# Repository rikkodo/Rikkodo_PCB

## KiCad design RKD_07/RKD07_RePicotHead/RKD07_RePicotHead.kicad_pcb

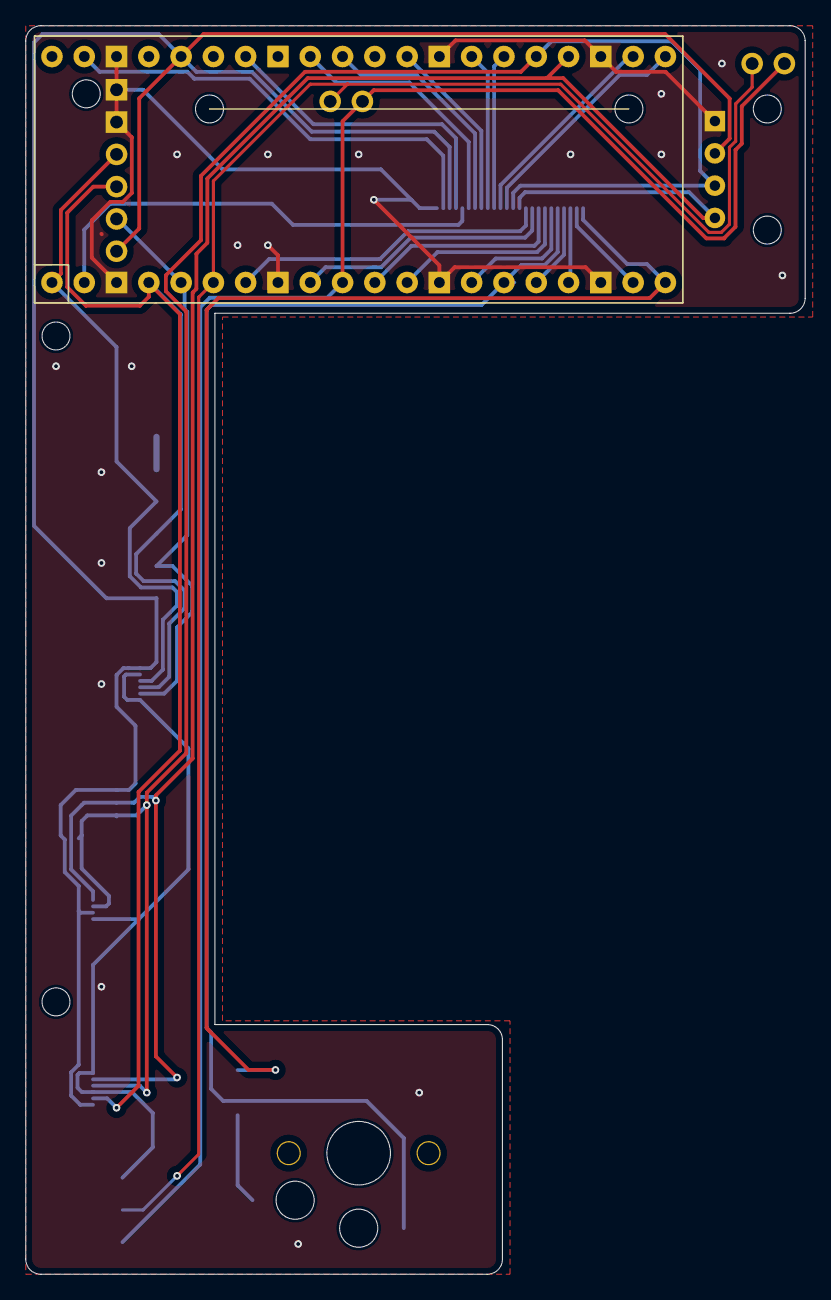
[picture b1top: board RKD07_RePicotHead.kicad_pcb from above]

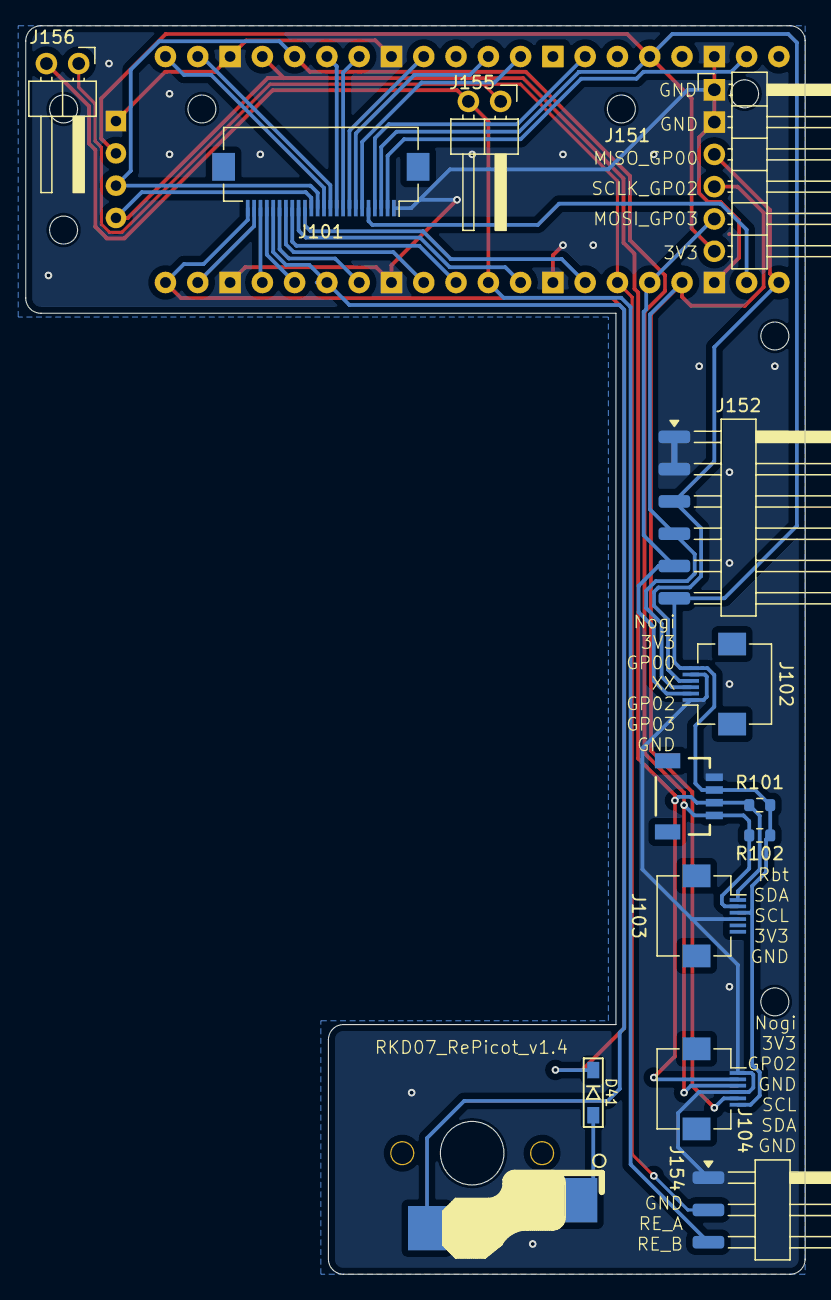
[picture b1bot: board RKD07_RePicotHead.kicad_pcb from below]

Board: 2 copper layers, 61.3 x 98.2 mm, 22 parts (12 on the bottom side), 30 nets.

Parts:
D41: D; Diode_SMD
J101: Conn_01x24; Hirose_FH12-24S-0.5SH_1x24-1MP_P0.50mm_Horizontal
J102, J103, J104: Conn_01x06; Hirose_FH12-6S-0.5SH_1x06-1MP_P0.50mm_Horizontal
J151: Conn_01x06; PinHeader_1x06_P2.54mm_Horizontal
J152: Conn_01x06; Harwin_M20-89006xx_1x06_P2.54mm_Horizontal
J153: Qwiic_RA; JST_SMD_1.0mm-4_Black
J154: Conn_01x02_Socket; Harwin_M20-89003xx_1x03_P2.54mm_Horizontal
J155, J156: Conn_01x02_Socket; PinHeader_1x02_P2.54mm_Horizontal
OL101: OLED; OLED_center_display
R101, R102: 1kΩ; R_0603_1608Metric
Ref**: Val**; m2_Screw_Hole
Ref**#2, Ref**#3, Ref**#4, Ref**#5: Val**; m2_Screw_Hole
SW41: SW_Push; rkd_Asm_ChocV1V2_Hotswap_1u
U101: Pico; rkd_RPi_Pico_TH_NODBG
UnifiedW**: rkd_unified_wid_BTM

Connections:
3V3: J101.3, J102.6, J103.3, J104.6, J151.6, J152.6, J153.2, OL101.3 (VCC), R101.1, R102.1, U101.36 (3V3)
COL0_L: J101.15, U101.7 (GPIO5)
COL1_L: J101.16, U101.9 (GPIO6)
COL2_L: J101.17, U101.11 (GPIO8)
COL3_L: J101.18, U101.12 (GPIO9)
COL4_L: J101.19, U101.14 (GPIO10)
COL5_L: J101.20, SW41.2, U101.15 (GPIO11)
COL6_L: J101.12, U101.21 (GPIO16)
COL7_L: J101.11, U101.22 (GPIO17)
COL8_L: J101.10, U101.26 (GPIO20)
COL9_L: J101.9, U101.27 (GPIO21)
COL10_L: J101.8, U101.29 (GPIO22)
COL11_L: J101.7, U101.31 (GPIO26_ADC0)
COL12_L: J101.6, U101.32 (GPIO27_ADC1)
COL13_L: J101.5, U101.2 (GPIO1)
GND: J101.1, J102.1, J102.5, J103.4, J104.1, J104.4, J151.1, J151.2, J152.1, J152.2, J153.1, J154.1, OL101.4 (GND), U101.3 (GND), U101.8 (GND), U101.13 (GND), U101.18 (GND), U101.23 (GND), U101.28 (GND), U101.38 (GND)
GP00_MISO: J102.4, J151.3, J152.3, U101.1 (GPIO0)
GP02_SCLK: J102.3, J104.5, J151.4, J152.4, U101.4 (GPIO2)
GP03_MOSI: J102.2, J151.5, J152.5, U101.5 (GPIO3)
GP04: J154.2, J155.1, J156.1, U101.6 (GPIO4)
GP07: J154.3, J155.2, J156.2, U101.10 (GPIO7)
unnamed: D41.2 (A), SW41.1
ROW0_L: J101.4, U101.34 (GPIO28_ADC2)
ROW1_L: J101.21, U101.16 (GPIO12)
ROW2_L: J101.22, U101.17 (GPIO13)
ROW3_L: J101.23, U101.19 (GPIO14)
ROW4_L: D41.1 (K), J101.24, U101.20 (GPIO15)
SCL/TX_L: J101.13, J103.2, J104.3, J153.4, OL101.2 (SCL), R102.2, U101.25 (GPIO19)
SDA/SCK_L: J101.14, J103.1, J104.2, J153.3, OL101.1 (SDA), R101.2, U101.24 (GPIO18)
VCC: J101.2, U101.39 (VSYS)

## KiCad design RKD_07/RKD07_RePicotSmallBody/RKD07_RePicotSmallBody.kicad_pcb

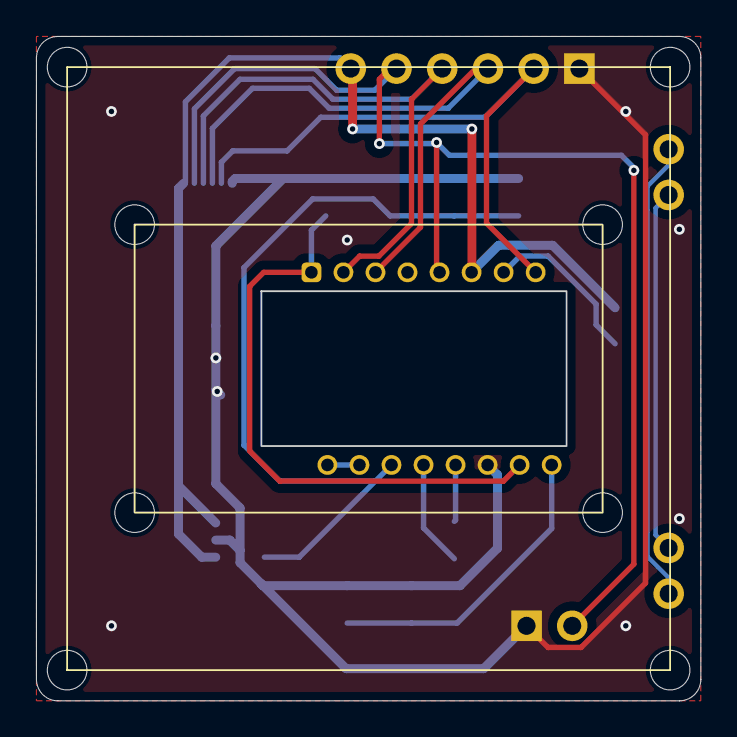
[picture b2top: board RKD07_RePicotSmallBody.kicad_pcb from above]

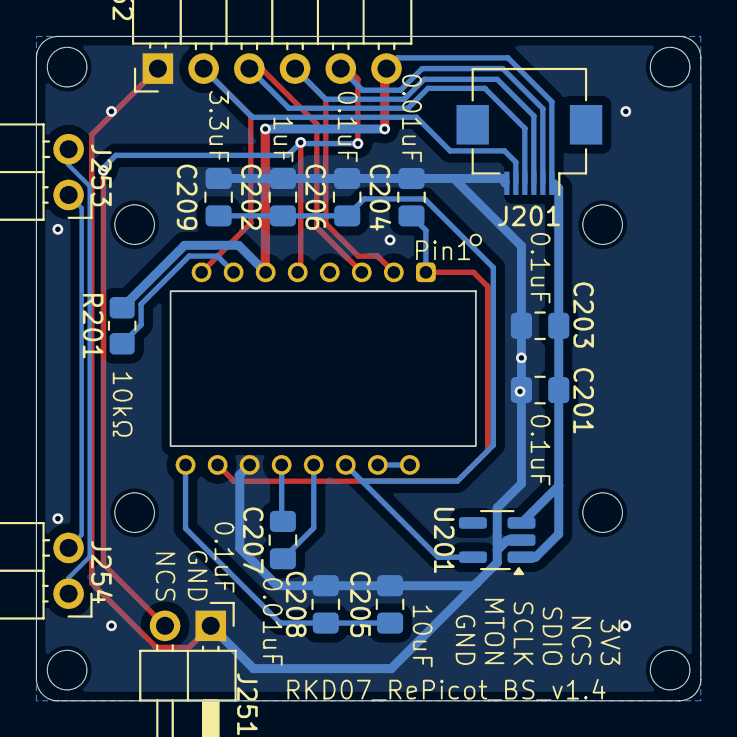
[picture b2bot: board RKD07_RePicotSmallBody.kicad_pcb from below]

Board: 2 copper layers, 36.9 x 36.9 mm, 18 parts (16 on the bottom side), 15 nets.

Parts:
C201, C203, C206, C207: 0.1uF X7R; C_0805_2012Metric_Pad1.18x1.45mm_HandSolder
C202: 1uF; C_0805_2012Metric_Pad1.18x1.45mm_HandSolder
C204, C208: 0.01uF X7R; C_0805_2012Metric_Pad1.18x1.45mm_HandSolder
C205: 10uF X7R; C_0805_2012Metric_Pad1.18x1.45mm_HandSolder
C209: 3.3uF/16V; C_0805_2012Metric_Pad1.18x1.45mm_HandSolder
J201: Conn_01x06; Hirose_FH12-6S-0.5SH_1x06-1MP_P0.50mm_Horizontal
J251, J253, J254: Conn_01x02_Socket; PinHeader_1x02_P2.54mm_Horizontal
J252: Conn_01x06; PinHeader_1x06_P2.54mm_Horizontal
Picot**: rkd_picot5400_BTM
R201: 10k; R_0805_2012Metric_Pad1.20x1.40mm_HandSolder
U201: TLV70019DDCR; SOT-23-5_HandSoldering
U202: PMW3610DM-SUDU

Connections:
1V9_E: C202.1, C206.1, C209.1, U201.5 (OUT), U202.14 (VDD)
3V3_E: C201.1, C203.1, J201.1, J252.6, R201.2, U201.1 (IN), U201.3 (EN), U202.6 (VDDIO)
GND_E: C201.2, C202.2, C203.2, C204.2, C205.2, C206.2, C208.2, C209.2, J201.6, J251.1, J252.1, U201.2 (GND), U202.11 (GND)
GP00_MISO_E: J201.3, J252.4, U202.2 (SDIO)
GP02_SCLK_E: J201.4, J252.3, U202.3 (SCLK)
GP03_MOSI_E: J201.5, J252.2, U202.8 (MOTION)
GP04_E: J253.1, J254.2
GP07_E: J253.2, J254.1
NCS_E: J201.2, J251.2, J252.5, U202.5 (NCS)
unnamed: C204.1, U202.1 (+VCSEL), U202.10 (PASS_T)
unnamed: U202.15 (XYLASER), U202.16 (-VCSEL)
unnamed: C207.1, U202.13 (CN)
unnamed: C207.2, U202.12 (CP)
unnamed: R201.1, U202.7 (NRESET)
unnamed: C205.1, C208.1, U202.9 (VCP)

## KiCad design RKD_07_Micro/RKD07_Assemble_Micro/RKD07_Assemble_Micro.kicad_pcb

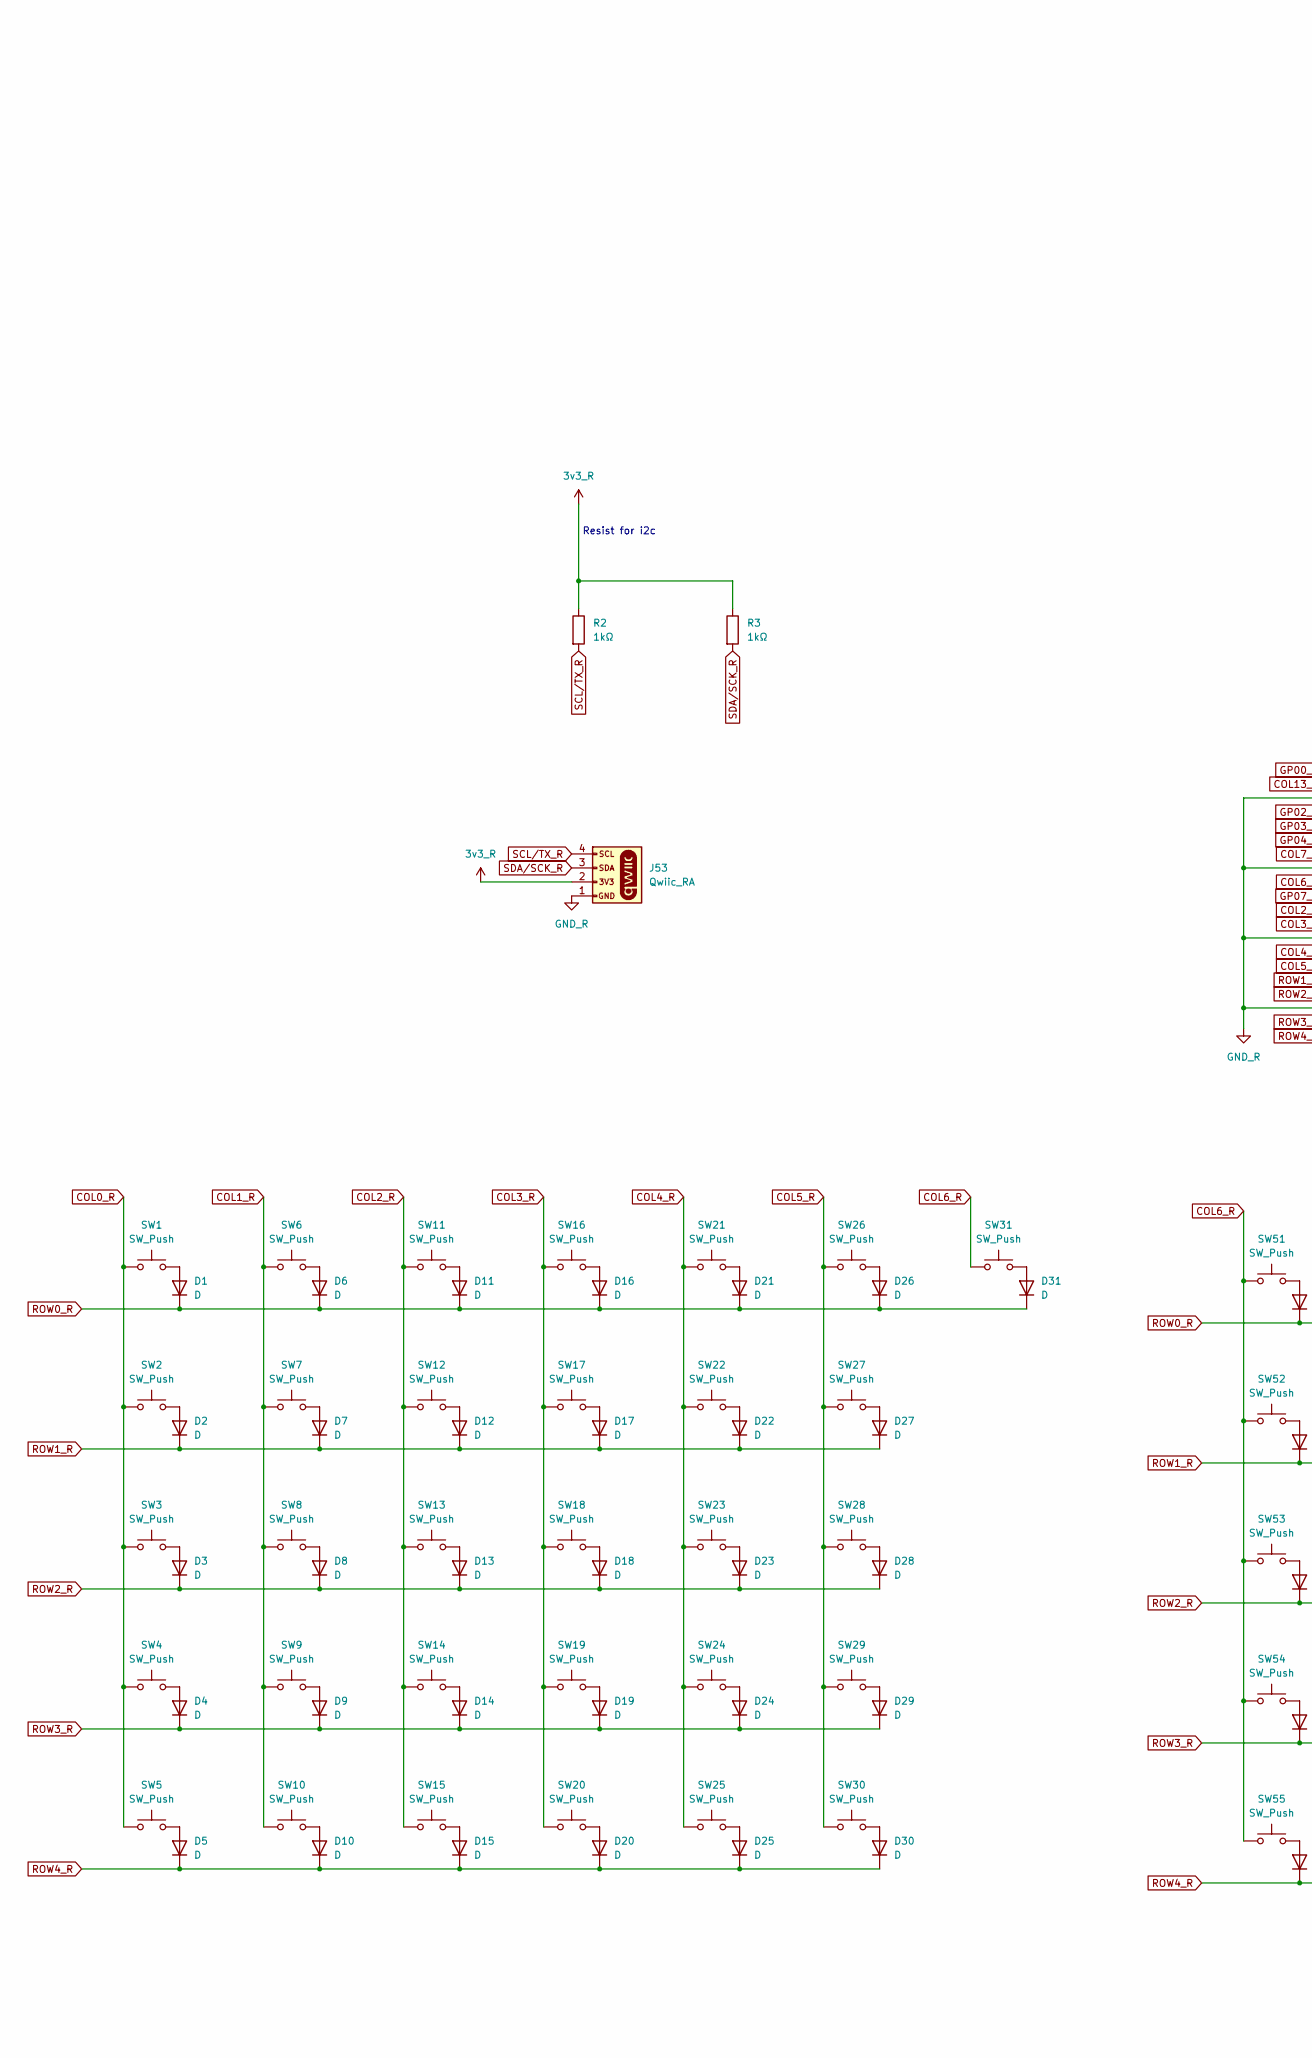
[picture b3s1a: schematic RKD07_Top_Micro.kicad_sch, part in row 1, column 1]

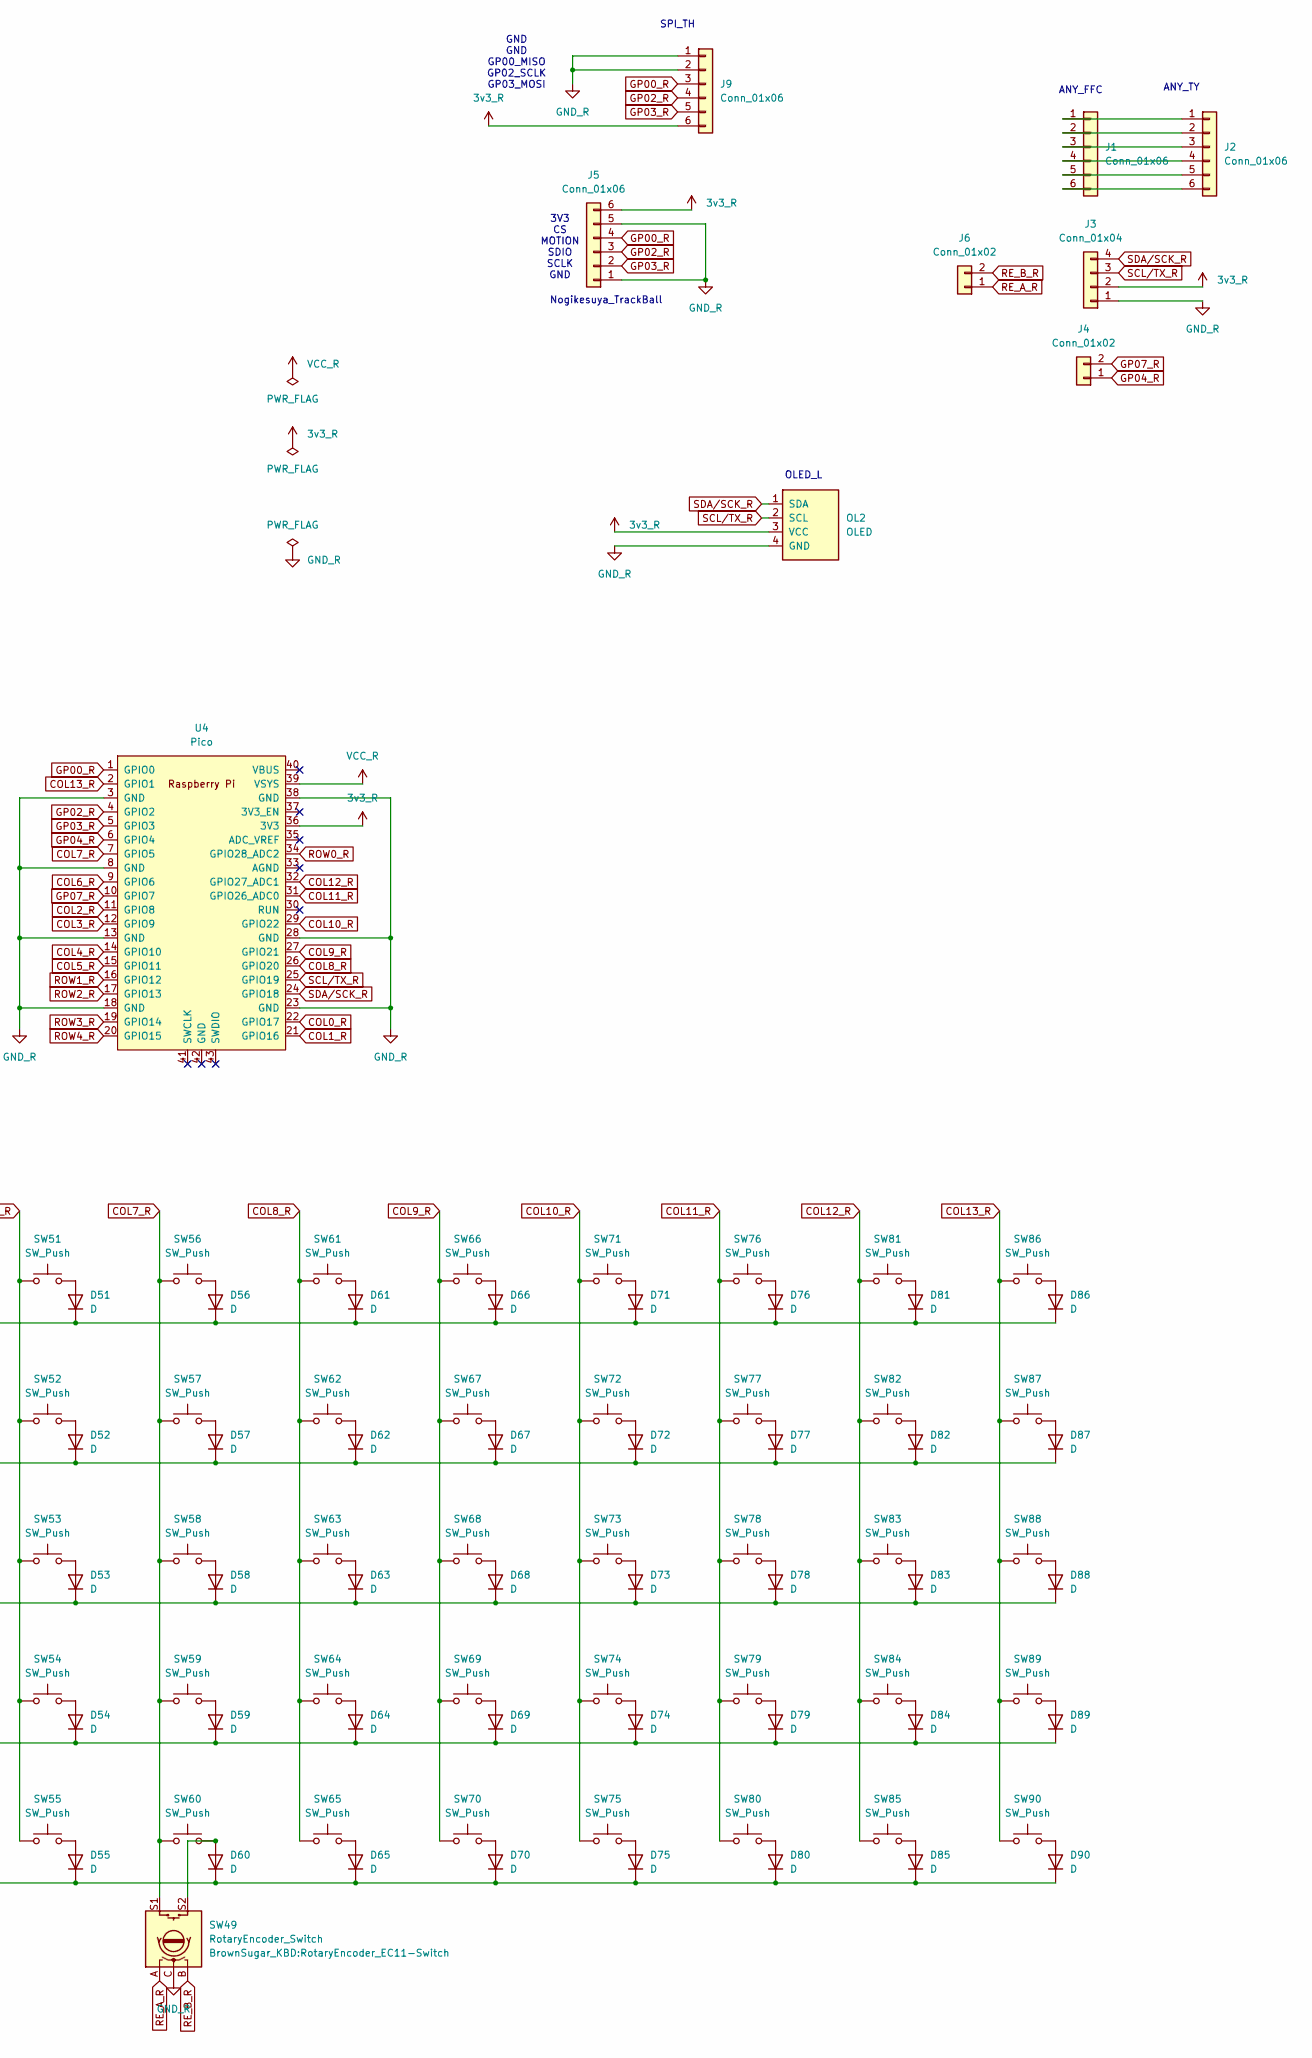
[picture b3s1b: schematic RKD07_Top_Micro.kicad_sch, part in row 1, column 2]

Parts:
D1, D2, D3, D4, D5, D6, D7, D8, D9, D10, D11, D12, D13, D14, D15, D16, D17, D18, D19, D20, D21, D22, D23, D24, D25, D26, D27, D28, D29, D30, D31, D51, D52, D53, D54, D55, D56, D57, D58, D59, D60, D61, D62, D63, D64, D65, D66, D67, D68, D69, D70, D71, D72, D73, D74, D75, D76, D77, D78, D79, D80, D81, D82, D83, D84, D85, D86, D87, D88, D89, D90: D; Diode_SMD
J1, J5: Conn_01x06; Hirose_FH12-6S-0.5SH_1x06-1MP_P0.50mm_Horizontal
J2, J9: Conn_01x06; PinHeader_1x06_P2.54mm_Vertical
J3: Conn_01x04; PinHeader_1x04_P2.54mm_Vertical
J4, J6: Conn_01x02; PinHeader_1x02_P2.54mm_Vertical
J53: Qwiic_RA; JST_SMD_1.0mm-4_Black
OL2: OLED; OLED_center_display
R2, R3: 1kΩ; R_0603_1608Metric
SW1, SW6, SW7, SW8, SW9, SW11, SW12, SW13, SW14, SW16, SW17, SW18, SW19, SW21, SW22, SW23, SW24, SW26, SW27, SW28, SW29, SW31, SW51, SW52, SW54, SW56, SW57, SW58, SW59, SW61, SW62, SW63, SW64, SW66, SW67, SW68, SW69, SW70, SW71, SW72, SW73, SW74, SW75, SW76, SW77, SW78, SW79, SW80, SW81, SW82, SW83, SW84, SW85, SW89, SW90: SW_Push; rkd_pushsw_2_1u
SW2, SW60, SW87: SW_Push; rkd_pushsw_2_1.5u
SW3: SW_Push; rkd_pushsw_2_1.75u
SW4, SW86: SW_Push; rkd_pushsw_2_2u
SW5, SW10, SW15, SW20, SW30, SW53, SW55, SW65: SW_Push; rkd_pushsw_2_1.25u
SW25, SW88: SW_Push; rkd_pushsw_2_2.25u
SW49: RotaryEncoder_Switch; RotaryEncoder_EC11-Switch
U4: Pico; rkd_RPi_Pico_TH_NODBG

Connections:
3v3_R: J3.2, J5.6, J9.6, J53.2, OL2.3 (VCC), R2.1, R3.1, U4.36 (3V3)
COL0_R: SW1.2, SW2.2, SW3.2, SW4.2, SW5.2, U4.22 (GPIO17)
COL1_R: SW6.2, SW7.2, SW8.2, SW9.2, SW10.2, U4.21 (GPIO16)
COL2_R: SW11.2, SW12.2, SW13.2, SW14.2, SW15.2, U4.11 (GPIO8)
COL3_R: SW16.2, SW17.2, SW18.2, SW19.2, SW20.2, U4.12 (GPIO9)
COL4_R: SW21.2, SW22.2, SW23.2, SW24.2, SW25.2, U4.14 (GPIO10)
COL5_R: SW26.2, SW27.2, SW28.2, SW29.2, SW30.2, U4.15 (GPIO11)
COL6_R: SW31.2, SW51.2, SW52.2, SW53.2, SW54.2, SW55.2, U4.9 (GPIO6)
COL7_R: SW49.S1, SW56.2, SW57.2, SW58.2, SW59.2, SW60.2, U4.7 (GPIO5)
COL8_R: SW61.2, SW62.2, SW63.2, SW64.2, SW65.2, U4.26 (GPIO20)
COL9_R: SW66.2, SW67.2, SW68.2, SW69.2, SW70.2, U4.27 (GPIO21)
COL10_R: SW71.2, SW72.2, SW73.2, SW74.2, SW75.2, U4.29 (GPIO22)
COL11_R: SW76.2, SW77.2, SW78.2, SW79.2, SW80.2, U4.31 (GPIO26_ADC0)
COL12_R: SW81.2, SW82.2, SW83.2, SW84.2, SW85.2, U4.32 (GPIO27_ADC1)
COL13_R: SW86.2, SW87.2, SW88.2, SW89.2, SW90.2, U4.2 (GPIO1)
GND_R: J3.1, J5.1, J5.5, J9.1, J9.2, J53.1, OL2.4 (GND), SW49.C, U4.3 (GND), U4.8 (GND), U4.13 (GND), U4.18 (GND), U4.23 (GND), U4.28 (GND), U4.38 (GND)
GP00_R: J5.4, J9.3, U4.1 (GPIO0)
GP02_R: J5.3, J9.4, U4.4 (GPIO2)
GP03_R: J5.2, J9.5, U4.5 (GPIO3)
GP04_R: J4.1, U4.6 (GPIO4)
GP07_R: J4.2, U4.10 (GPIO7)
unnamed: D1.2 (A), SW1.1
unnamed: D2.2 (A), SW2.1
unnamed: D3.2 (A), SW3.1
unnamed: D4.2 (A), SW4.1
unnamed: D5.2 (A), SW5.1
unnamed: D6.2 (A), SW6.1
unnamed: D7.2 (A), SW7.1
unnamed: D8.2 (A), SW8.1
unnamed: D9.2 (A), SW9.1
unnamed: D10.2 (A), SW10.1
unnamed: D11.2 (A), SW11.1
unnamed: D12.2 (A), SW12.1
unnamed: D13.2 (A), SW13.1
unnamed: D14.2 (A), SW14.1
unnamed: D15.2 (A), SW15.1
unnamed: D16.2 (A), SW16.1
unnamed: D17.2 (A), SW17.1
unnamed: D18.2 (A), SW18.1
unnamed: D19.2 (A), SW19.1
unnamed: D20.2 (A), SW20.1
unnamed: D21.2 (A), SW21.1
unnamed: D22.2 (A), SW22.1
unnamed: D23.2 (A), SW23.1
unnamed: D24.2 (A), SW24.1
unnamed: D25.2 (A), SW25.1
unnamed: D26.2 (A), SW26.1
unnamed: D27.2 (A), SW27.1
unnamed: D28.2 (A), SW28.1
unnamed: D29.2 (A), SW29.1
unnamed: D30.2 (A), SW30.1
unnamed: D31.2 (A), SW31.1
unnamed: D51.2 (A), SW51.1
unnamed: D52.2 (A), SW52.1
unnamed: D53.2 (A), SW53.1
unnamed: D54.2 (A), SW54.1
unnamed: D55.2 (A), SW55.1
unnamed: D56.2 (A), SW56.1
unnamed: D57.2 (A), SW57.1
unnamed: D58.2 (A), SW58.1
unnamed: D59.2 (A), SW59.1
unnamed: D60.2 (A), SW49.S2, SW60.1
unnamed: D61.2 (A), SW61.1
unnamed: D62.2 (A), SW62.1
unnamed: D63.2 (A), SW63.1
unnamed: D64.2 (A), SW64.1
unnamed: D65.2 (A), SW65.1
unnamed: D66.2 (A), SW66.1
unnamed: D67.2 (A), SW67.1
unnamed: D68.2 (A), SW68.1
unnamed: D69.2 (A), SW69.1
unnamed: D70.2 (A), SW70.1
unnamed: D71.2 (A), SW71.1
unnamed: D72.2 (A), SW72.1
unnamed: D73.2 (A), SW73.1
unnamed: D74.2 (A), SW74.1
unnamed: D75.2 (A), SW75.1
unnamed: D76.2 (A), SW76.1
unnamed: D77.2 (A), SW77.1
unnamed: D78.2 (A), SW78.1
unnamed: D79.2 (A), SW79.1
unnamed: D80.2 (A), SW80.1
unnamed: D81.2 (A), SW81.1
unnamed: D82.2 (A), SW82.1
unnamed: D83.2 (A), SW83.1
unnamed: D84.2 (A), SW84.1
unnamed: D85.2 (A), SW85.1
unnamed: D86.2 (A), SW86.1
unnamed: D87.2 (A), SW87.1
unnamed: D88.2 (A), SW88.1
unnamed: D89.2 (A), SW89.1
unnamed: D90.2 (A), SW90.1
unnamed: J1.1, J2.1
unnamed: J1.2, J2.2
unnamed: J1.3, J2.3
unnamed: J1.4, J2.4
unnamed: J1.5, J2.5
unnamed: J1.6, J2.6
RE_A_R: J6.1, SW49.A
RE_B_R: J6.2, SW49.B
ROW0_R: D1.1 (K), D6.1 (K), D11.1 (K), D16.1 (K), D21.1 (K), D26.1 (K), D31.1 (K), D51.1 (K), D56.1 (K), D61.1 (K), D66.1 (K), D71.1 (K), D76.1 (K), D81.1 (K), D86.1 (K), U4.34 (GPIO28_ADC2)
ROW1_R: D2.1 (K), D7.1 (K), D12.1 (K), D17.1 (K), D22.1 (K), D27.1 (K), D52.1 (K), D57.1 (K), D62.1 (K), D67.1 (K), D72.1 (K), D77.1 (K), D82.1 (K), D87.1 (K), U4.16 (GPIO12)
ROW2_R: D3.1 (K), D8.1 (K), D13.1 (K), D18.1 (K), D23.1 (K), D28.1 (K), D53.1 (K), D58.1 (K), D63.1 (K), D68.1 (K), D73.1 (K), D78.1 (K), D83.1 (K), D88.1 (K), U4.17 (GPIO13)
ROW3_R: D4.1 (K), D9.1 (K), D14.1 (K), D19.1 (K), D24.1 (K), D29.1 (K), D54.1 (K), D59.1 (K), D64.1 (K), D69.1 (K), D74.1 (K), D79.1 (K), D84.1 (K), D89.1 (K), U4.19 (GPIO14)
ROW4_R: D5.1 (K), D10.1 (K), D15.1 (K), D20.1 (K), D25.1 (K), D30.1 (K), D55.1 (K), D60.1 (K), D65.1 (K), D70.1 (K), D75.1 (K), D80.1 (K), D85.1 (K), D90.1 (K), U4.20 (GPIO15)
SCL/TX_R: J3.3, J53.4, OL2.2 (SCL), R2.2, U4.25 (GPIO19)
SDA/SCK_R: J3.4, J53.3, OL2.1 (SDA), R3.2, U4.24 (GPIO18)
VCC_R: U4.39 (VSYS)

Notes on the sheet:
GND GND GP00_MISO GP02_SCLK GP03_MOSI
Resist for i2c
ANY_TY
3V3 CS MOTION SDIO SCLK GND
ANY_FFC
Nogikesuya_TrackBall
SPI_TH
OLED_L

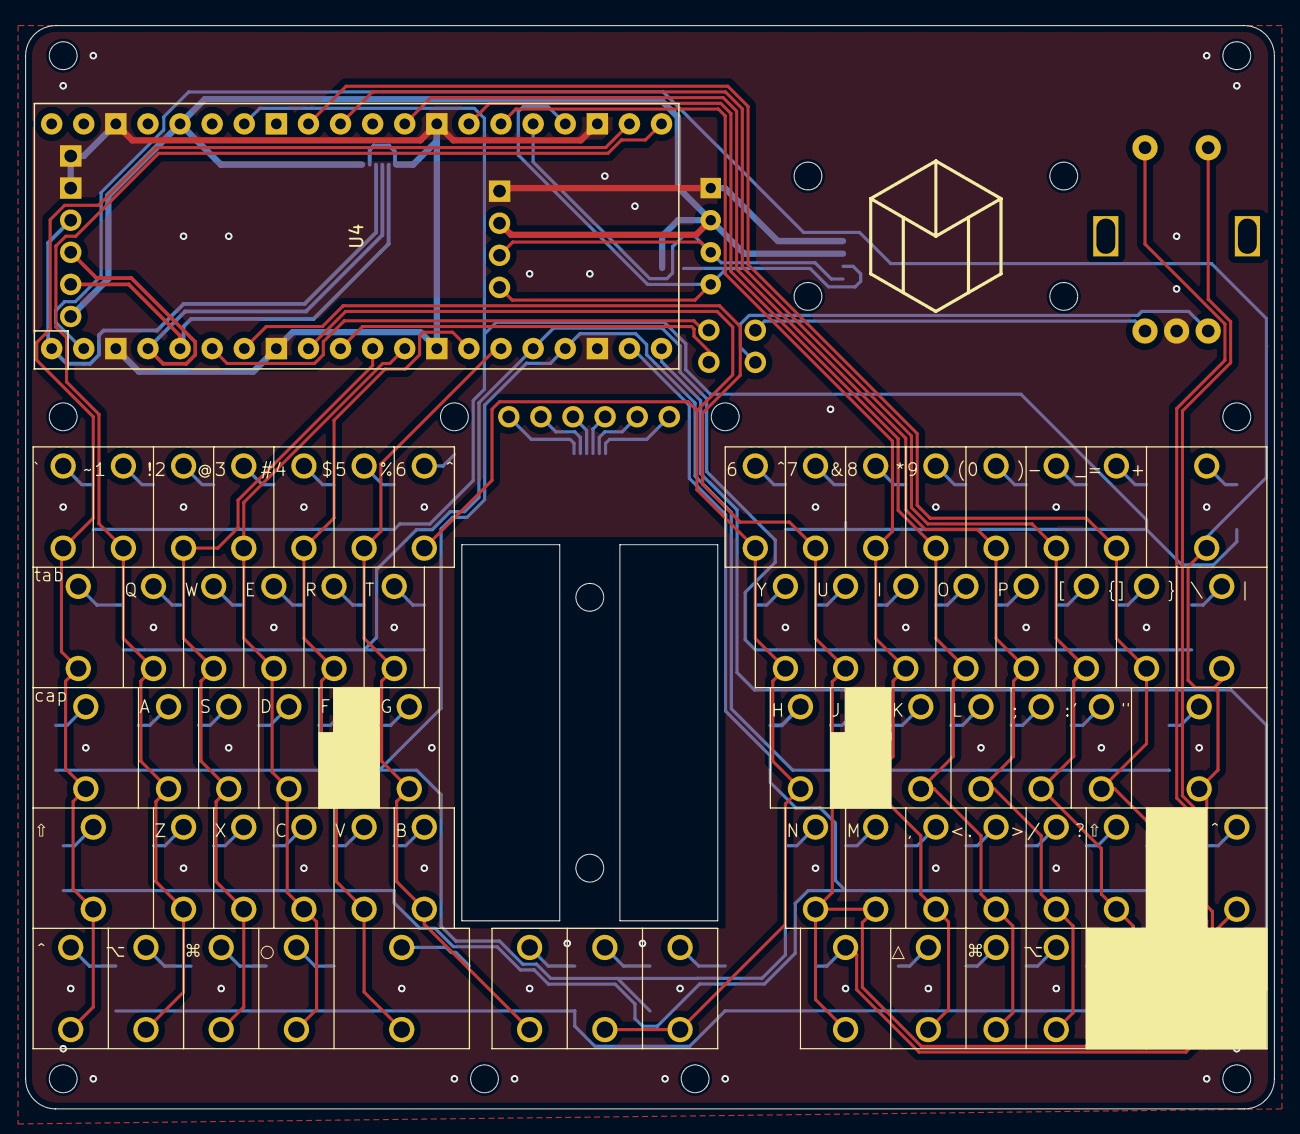
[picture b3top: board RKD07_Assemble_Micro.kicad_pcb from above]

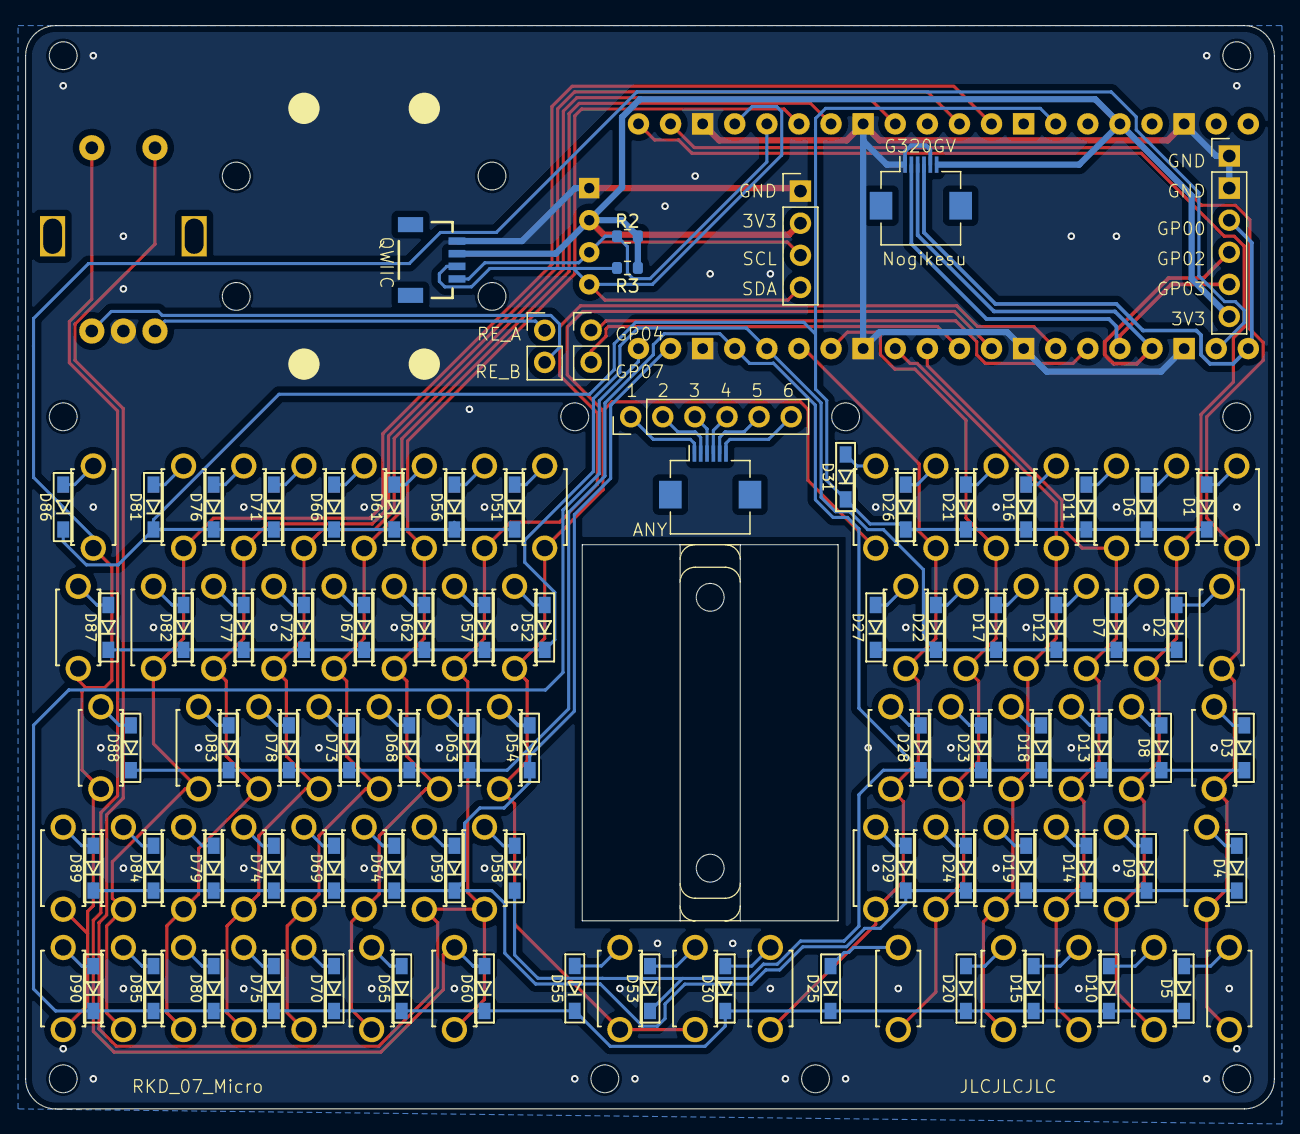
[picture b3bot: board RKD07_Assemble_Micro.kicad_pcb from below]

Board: 2 copper layers, 98.8 x 85.7 mm, 170 parts (10 on the bottom side), 107 nets.

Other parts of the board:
Point1: Guard_Screw_Hall; rkd_Guard_Screw_Hall
Ref**: Val**; m2_Screw_Hole
Ref**#2, Ref**#3, Ref**#4, Ref**#5, Ref**#6, Ref**#7, Ref**#8, Ref**#9, Ref**#10, Ref**#11, Ref**#12, Ref**#13, Ref**#14: Val**; m2_Screw_Hole

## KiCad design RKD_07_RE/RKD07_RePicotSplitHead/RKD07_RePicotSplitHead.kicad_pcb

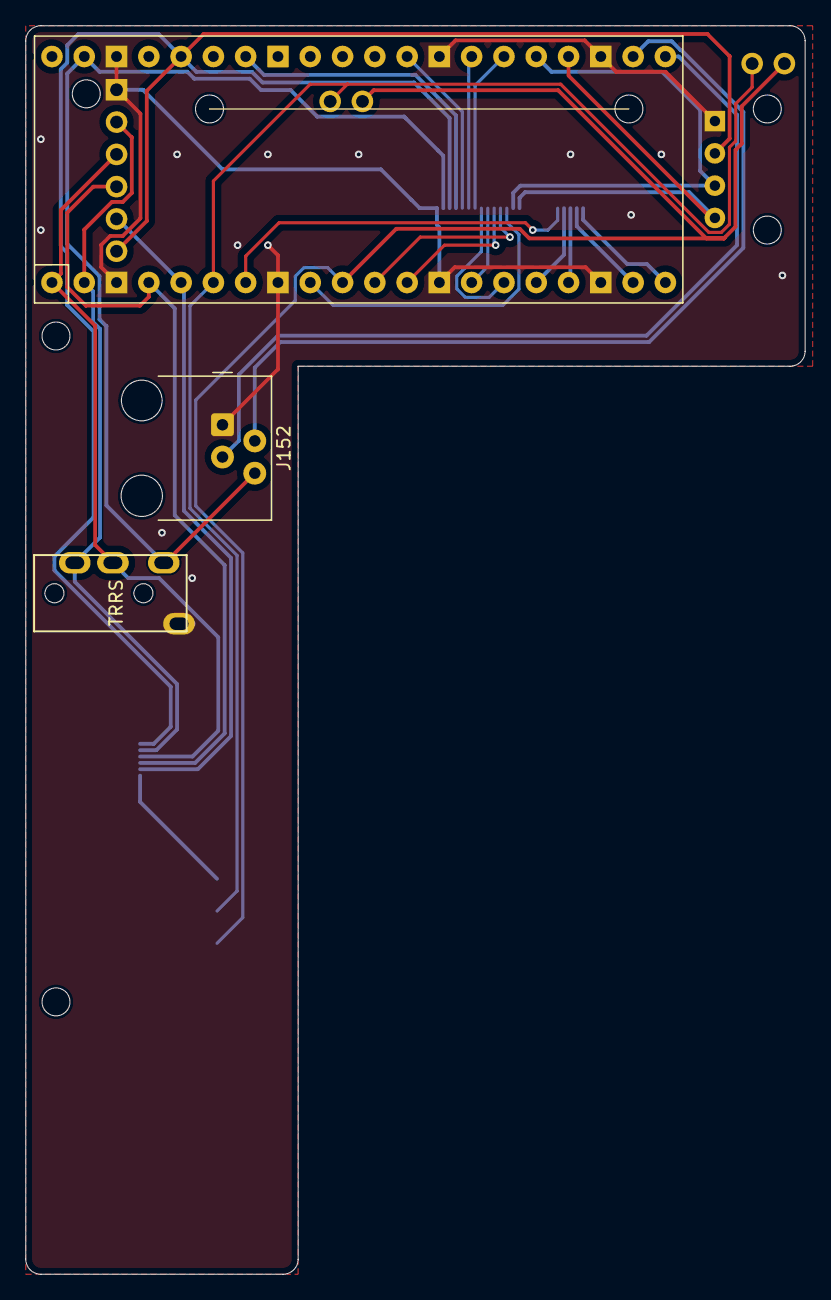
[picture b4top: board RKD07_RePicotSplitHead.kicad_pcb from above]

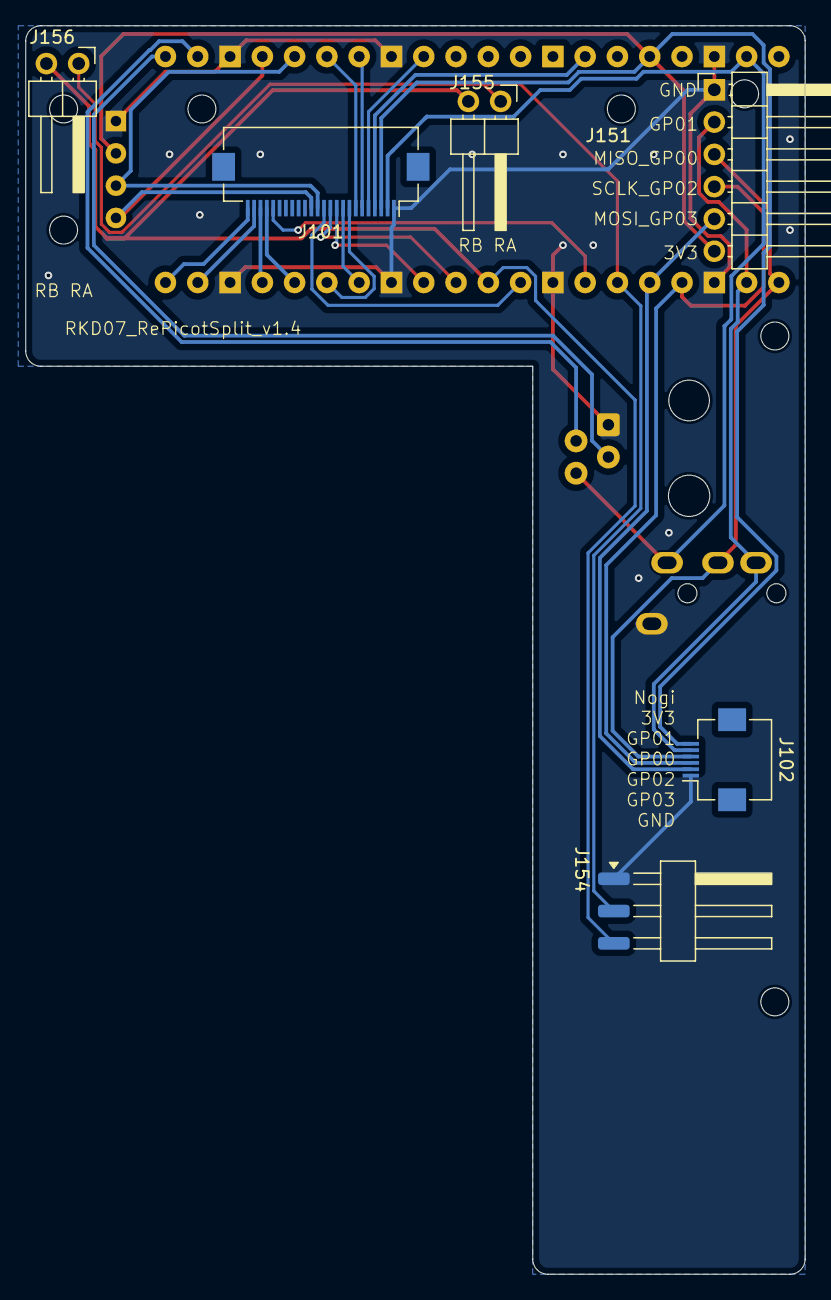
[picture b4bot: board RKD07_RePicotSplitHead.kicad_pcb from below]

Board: 2 copper layers, 61.3 x 98.2 mm, 16 parts (6 on the bottom side), 27 nets.

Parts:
J101: Conn_01x24; Hirose_FH12-24S-0.5SH_1x24-1MP_P0.50mm_Horizontal
J102: Conn_01x06; Hirose_FH12-6S-0.5SH_1x06-1MP_P0.50mm_Horizontal
J151: Conn_01x06; PinHeader_1x06_P2.54mm_Horizontal
J152: RJ9; RJ9_Evercom_5301-440xxx_Horizontal
J153: TRRS; TRRS_PJ-320A
J154: Conn_01x02_Socket; Harwin_M20-89003xx_1x03_P2.54mm_Horizontal
J155, J156: Conn_01x02_Socket; PinHeader_1x02_P2.54mm_Horizontal
OL101: OLED; OLED_center_display
Ref**: Val**; m2_Screw_Hole
Ref**#2, Ref**#3, Ref**#4, Ref**#5: Val**; m2_Screw_Hole
U101: Pico; rkd_RPi_Pico_TH_NODBG
UnifiedW**: rkd_unified_wid_BTM

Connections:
3V3: J101.3, J102.6, J151.6, OL101.3 (VCC), U101.36 (3V3)
COL5_L: J101.20, U101.7 (GPIO5)
COL6_L: J101.12, U101.9 (GPIO6)
COL7_L: J101.11, U101.11 (GPIO8)
COL8_L: J101.10, U101.12 (GPIO9)
COL9_L: J101.9, U101.14 (GPIO10)
COL10_L: J101.8, U101.15 (GPIO11)
COL11_L: J101.7, U101.26 (GPIO20)
COL12_L: J101.6, U101.27 (GPIO21)
COL13_L: J101.5, U101.29 (GPIO22)
GND: J101.1, J102.1, J151.1, J152.1, J153.A, J154.1, OL101.4 (GND), U101.3 (GND), U101.8 (GND), U101.13 (GND), U101.18 (GND), U101.23 (GND), U101.28 (GND), U101.38 (GND)
GP00_MISO: J102.4, J151.3, J153.C, U101.1 (GPIO0)
GP01_NCS: J102.5, J151.2, J153.B, U101.2 (GPIO1)
GP02_SCLK: J102.3, J151.4, U101.4 (GPIO2)
GP03_MOSI: J102.2, J151.5, U101.5 (GPIO3)
GP04: J154.2, J155.1, J156.1, U101.6 (GPIO4)
GP07: J154.3, J155.2, J156.2, U101.10 (GPIO7)
GP16_TX: J152.3, U101.21 (GPIO16)
GP17_RX: J152.2, U101.22 (GPIO17)
ROW0_L: J101.4, U101.34 (GPIO28_ADC2)
ROW1_L: J101.21, U101.16 (GPIO12)
ROW2_L: J101.22, U101.17 (GPIO13)
ROW3_L: J101.23, U101.19 (GPIO14)
ROW4_L: J101.24, U101.20 (GPIO15)
SCL/TX_L: J101.13, OL101.2 (SCL), U101.25 (GPIO19)
SDA/SCK_L: J101.14, OL101.1 (SDA), U101.24 (GPIO18)
VCC: J101.2, J152.4, J153.D, U101.39 (VSYS)
